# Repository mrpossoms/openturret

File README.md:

# openturret
Opensource designs and software for autonomously aiming gimble

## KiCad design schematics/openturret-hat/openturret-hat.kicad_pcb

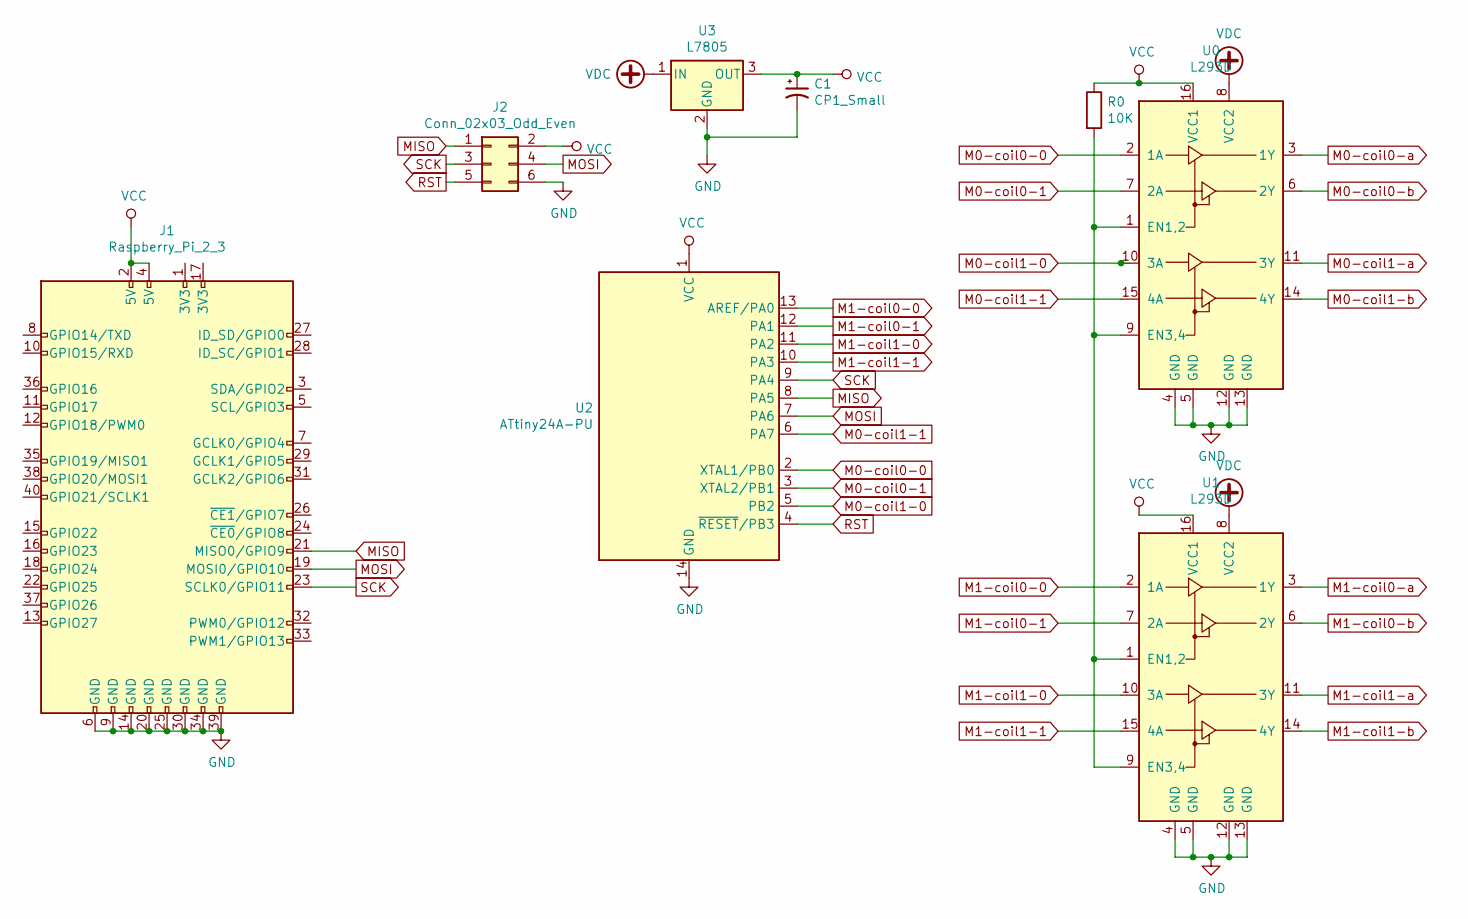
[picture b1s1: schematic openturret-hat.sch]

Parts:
C1: CP1_Small; CP_Radial_D5.0mm_P2.50mm
J1: Raspberry_Pi_2_3; PinHeader_2x20_P2.54mm_Vertical
J2: Conn_02x03_Odd_Even; PinHeader_2x03_P2.54mm_Vertical
R0: 10K; R_Axial_DIN0207_L6.3mm_D2.5mm_P2.54mm_Vertical
U0, U1: L293D; DIP-16_W7.62mm
U2: ATtiny24A-PU; DIP-14_W7.62mm
U3: L7805; TO-220-3_Vertical

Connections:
GND: C1.2, J1.6 (GND), J1.9 (GND), J1.14 (GND), J1.20 (GND), J1.25 (GND), J1.30 (GND), J1.34 (GND), J1.39 (GND), J2.6, U0.4 (GND), U0.5 (GND), U0.12 (GND), U0.13 (GND), U1.4 (GND), U1.5 (GND), U1.12 (GND), U1.13 (GND), U2.14 (GND), U3.2 (GND)
M0-coil0-0: U0.2 (1A), U2.2 (XTAL1/PB0)
M0-coil0-1: U0.7 (2A), U2.3 (XTAL2/PB1)
M0-coil0-a: U0.3 (1Y)
M0-coil0-b: U0.6 (2Y)
M0-coil1-0: U0.10 (3A), U2.5 (PB2)
M0-coil1-1: U0.15 (4A), U2.6 (PA7)
M0-coil1-a: U0.11 (3Y)
M0-coil1-b: U0.14 (4Y)
M1-coil0-0: U1.2 (1A), U2.13 (AREF/PA0)
M1-coil0-1: U1.7 (2A), U2.12 (PA1)
M1-coil0-a: U1.3 (1Y)
M1-coil0-b: U1.6 (2Y)
M1-coil1-0: U1.10 (3A), U2.11 (PA2)
M1-coil1-1: U1.15 (4A), U2.10 (PA3)
M1-coil1-a: U1.11 (3Y)
M1-coil1-b: U1.14 (4Y)
MISO: J1.21 (MISO0/GPIO9), J2.1, U2.8 (PA5)
MOSI: J1.19 (MOSI0/GPIO10), J2.4, U2.7 (PA6)
unnamed: R0.2, U0.1 (EN1,2), U0.9 (EN3,4), U1.1 (EN1,2), U1.9 (EN3,4)
RST: J2.5, U2.4 (~RESET~/PB3)
SCK: J1.23 (SCLK0/GPIO11), J2.3, U2.9 (PA4)
VCC: C1.1, J1.2 (5V), J1.4 (5V), J2.2, R0.1, U0.16 (VCC1), U1.16 (VCC1), U2.1 (VCC), U3.3 (OUT)
VDC: U0.8 (VCC2), U1.8 (VCC2), U3.1 (IN)

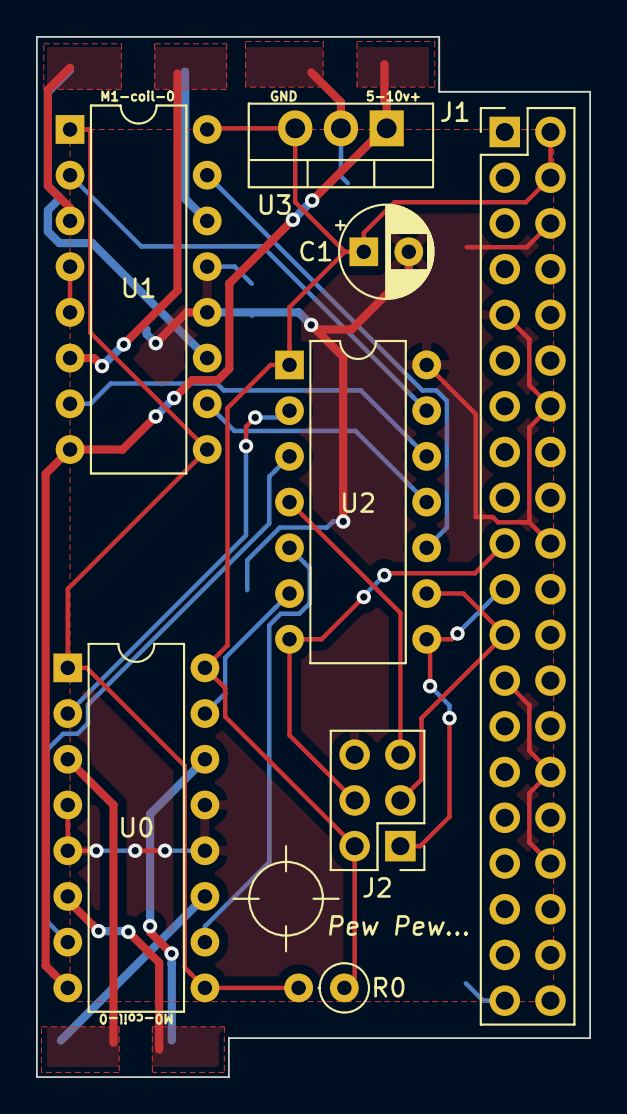
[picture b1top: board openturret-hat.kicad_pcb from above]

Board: 2 copper layers, 30.7 x 57.8 mm, 8 parts (0 on the bottom side), 16 nets.

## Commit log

2020-05-09 Stepper motor control bash scripts from a raspberry pi
2020-05-09 cad parts
2020-05-10 Schematics wip
2020-05-10 Starting firmware
2020-05-11 Working on firmware
2020-05-12 Fixed gpio manipulation, compiling
2020-05-12 WIP: firmware
2020-05-14 Working stepper control
2020-05-16 WIP on schematic and board layout
2020-05-16 openturret hat board rev 1
2020-05-16 Added spi driver
2020-05-21 First pass at SPI control
2020-05-27 Refactored to allow motor driver pins to reside on different ports
2020-06-16 Progress, master clock speed was too high for attiny slave with 1Mhz clock
2020-06-18 Very nearly working
2020-06-27 Getting closer!
2020-06-27 She works!
2020-07-03 Added init application code
2020-07-03 Working on turret control
2020-07-04 Fixed frame resolution issue
2020-07-06 Added stepper motor disabling for better thermal control
2020-07-06 Tracking working, though a bit laggy
2020-07-07 Some refactoring and calibration
2020-07-07 Getting better
2020-07-08 Better and better
2020-07-10 Some refactoring, some filtering
2020-07-12 Pretty good
2020-07-15 Color display red during frame waiting
2020-07-16 Moved feature matching into its own more reusable function
2020-07-16 Removed frame difference filtering
2020-07-19 increased spi clockspeed
2020-07-19 Adding target position derivative as a function of allowing movement
2020-07-20 More lively
2020-07-20 Switch to downsampling that takes averages across the downsampled groups of pixels in hopes of smoothing image quality
2020-07-21 Getting so close
2020-08-01 Disable motors option. Working on more robust featue tracking
2020-08-01 Working on improved feature matching
2020-08-01 Added feature set logic
2020-08-02 Added frame mapping step
2020-08-03 display FPS
2020-09-10 Added gif
2021-12-20 Added datasheets for mcu and half-h driver
2024-05-31 motor control in its own files
2024-05-31 Build and run on devices
2024-06-01 Refactoring and cleanup
2024-06-02 Working on refactoring program state
2024-06-05 More refactoring, building
